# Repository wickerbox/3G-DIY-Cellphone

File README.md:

cellphone3g
===========

Hardware for a 3G cellphone based on GSM/GPRS Arduino shield and damellis' DIY Cellphone.

[David A Mellis' DIY Cellphone 2G 'Cellphone Module'](http://web.media.mit.edu/~mellis/gsm/)

That project uses the 2G Quectel M10 Module which is pin compatible with the 3G Quectel UC15 Module. 

[Quectel GSM/GPRS M10](http://www.quectel.com/product/prodetail.aspx?id=14)

[Quectel UMTS/HSDPA UC15](http://www.quectel.com/product/prodetail.aspx?id=64)

[Quectel M10 and UC15 Design Compatibility](http://top-electronics.com/news/26/quectel-uc15-and-m10-design-compatibility.html)

**Differences**

1. Slightly different 3.3V-4.3V (UC15) vs 3.3V-4.6V (M10). Using a 3.7V battery is fine. MCP73831 recharges the 3.7V battery from the USB ... if the unit is powered off USB, it's at 4.2V which is on the high end. which is a little too close for comfort so I'd want to replace it with a USIM is the same. 

1. Frequency bands are slightly different but not much.

1. Pinout from controller will have to change. 

**Vocabulary**

GSM - Global System for Mobile Communications, 2G  
GPRS - General Packet Radio Services, packet data service on 2G and 3G  
UMTS - Universal Mobile Telecommunications System, 3G  
HSDPA - High-Speed Downlink Packet Access, allows higher speeds 3G speeds

**Reference**

"GSM (Global System for Mobile Communications, originally Groupe Spécial Mobile), is a standard developed by the European Telecommunications Standards Institute (ETSI) to describe protocols for second generation (2G) digital cellular networks used by mobile phones." [Wikipedia](http://en.wikipedia.org/wiki/GSM)

"General packet radio service (GPRS) is a packet oriented mobile data service on the 2G and 3G cellular communication system's global system for mobile communications (GSM)." [Wikipedia](http://en.wikipedia.org/wiki/General_Packet_Radio_Service)

"UMTS specifies a complete network system, which includes the radio access network (UMTS Terrestrial Radio Access Network, or UTRAN), the core network (Mobile Application Part, or MAP) and the authentication of users via SIM (subscriber identity module) cards." [Wikipedia](http://en.wikipedia.org/wiki/Universal_Mobile_Telecommunications_System)

"High-Speed Downlink Packet Access (HSDPA) is an enhanced 3G (third-generation) mobile-telephony communications protocol in the High-Speed Packet Access (HSPA) family, also dubbed 3.5G, 3G+, or Turbo 3G, which allows networks based on Universal Mobile Telecommunications System (UMTS) to have higher data-transfer speeds and capacity." [Wikipedia](en.wikipedia.org/wiki/High-Speed_Downlink_Packet_Access)

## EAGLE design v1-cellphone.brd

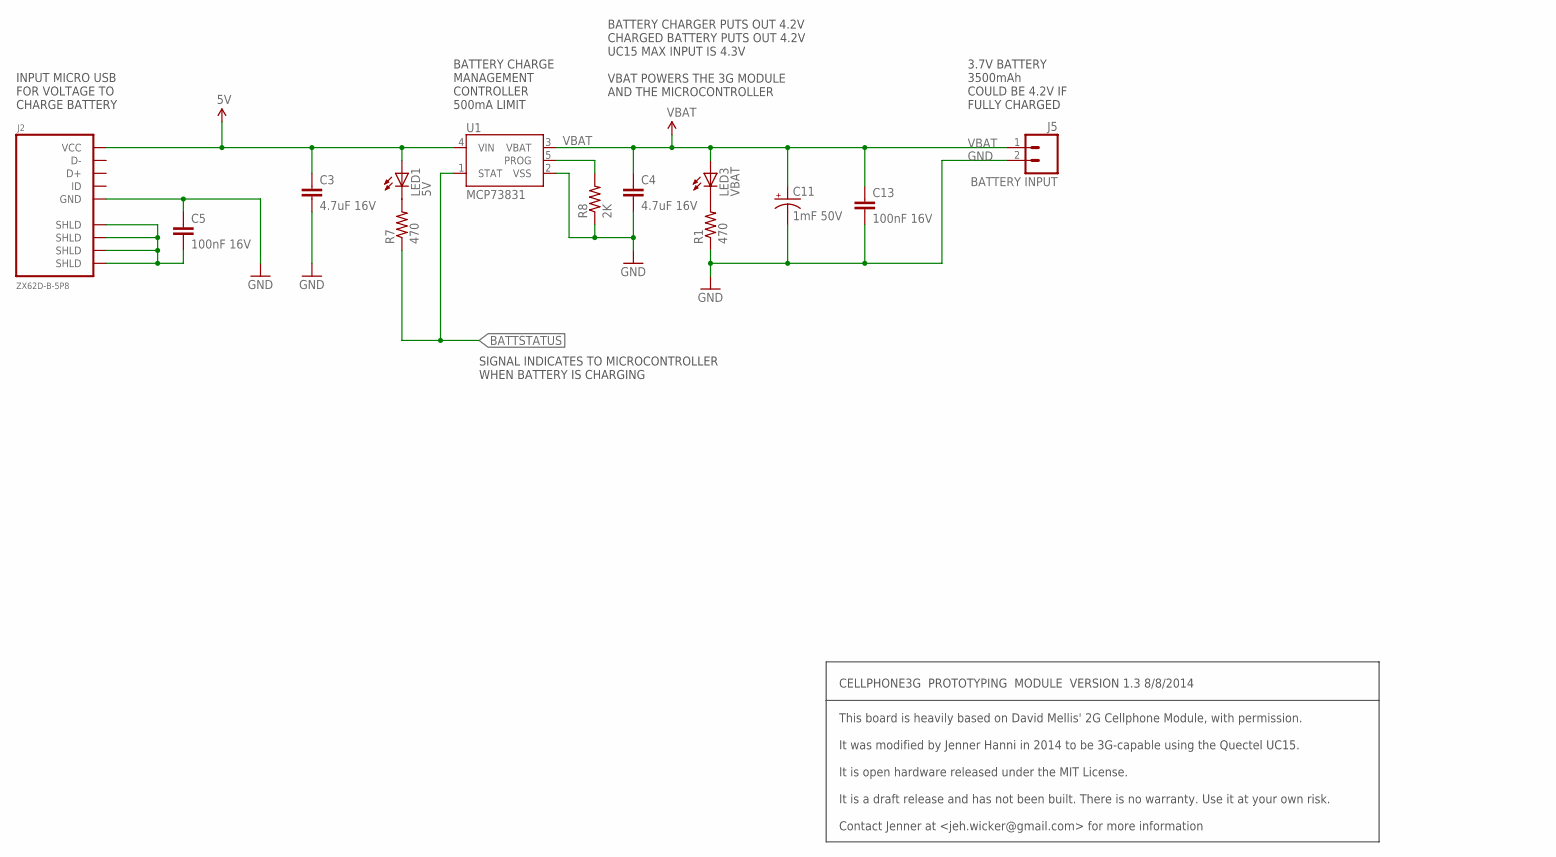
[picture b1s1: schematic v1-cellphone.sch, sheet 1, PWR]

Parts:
C3, C4: 4.7uF 16V; 0603-B
C5, C13: 100nF 16V; 0603-B
C11: 1mF 50V; CPOL-RADIAL-1000UF-25V
J2: ZX62D-B-5P8
J5: BATTERY INPUT; JST-2-SMD
LED1: 5V; CHIP-LED0603
LED3: VBAT; CHIP-LED0603
R1, R7: 470; 0603-B
R8: 2K; 0603-B
U1: MCP73831; SPARKFUN_SOT23-5

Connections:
5V: C3.1, J2.P1 (VCC), LED1.A, U1.4 (VIN); also elsewhere on the board
BATTSTATUS: R7.1, U1.1 (STAT); also elsewhere on the board
GND: C3.2, C4.2, C5.1, C11.2 (-), C13.2, J2.P5 (GND), J5.2 (1), R1.1, R8.1, U1.2 (VSS); also elsewhere on the board
unnamed: LED3.C, R1.2
unnamed: LED1.C, R7.2
PROG: R8.2, U1.5 (PROG)
SHLD: C5.2, J2.P$1 (SHLD), J2.P$2 (SHLD), J2.P$3 (SHLD), J2.P$4 (SHLD)
VBAT: C4.1, C11.1 (+), C13.1, J5.1 (2), LED3.A, U1.3 (VBAT); also elsewhere on the board

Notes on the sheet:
INPUT MICRO USB FOR VOLTAGE TO CHARGE BATTERY
BATTERY CHARGE MANAGEMENT CONTROLLER 500mA LIMIT
3.7V BATTERY 3500mAh COULD BE 4.2V IF FULLY CHARGED
BATTERY CHARGER PUTS OUT 4.2V CHARGED BATTERY PUTS OUT 4.2V UC15 MAX INPUT IS 4.3V VBAT POWERS THE 3G MODULE AND THE MICROCONTROLLER
CELLPHONE3G PROTOTYPING MODULE VERSION 1.3 8/8/2014
This board is heavily based on David Mellis' 2G Cellphone Module, with permission. It was modified by Jenner Hanni in 2014 to be 3G-capable using the Quectel UC15. It is open hardware released under the MIT License. It is a draft release and has not been built. There is no warranty. Use it at your 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
SIGNAL INDICATES TO MICROCONTROLLER WHEN BATTERY IS CHARGING

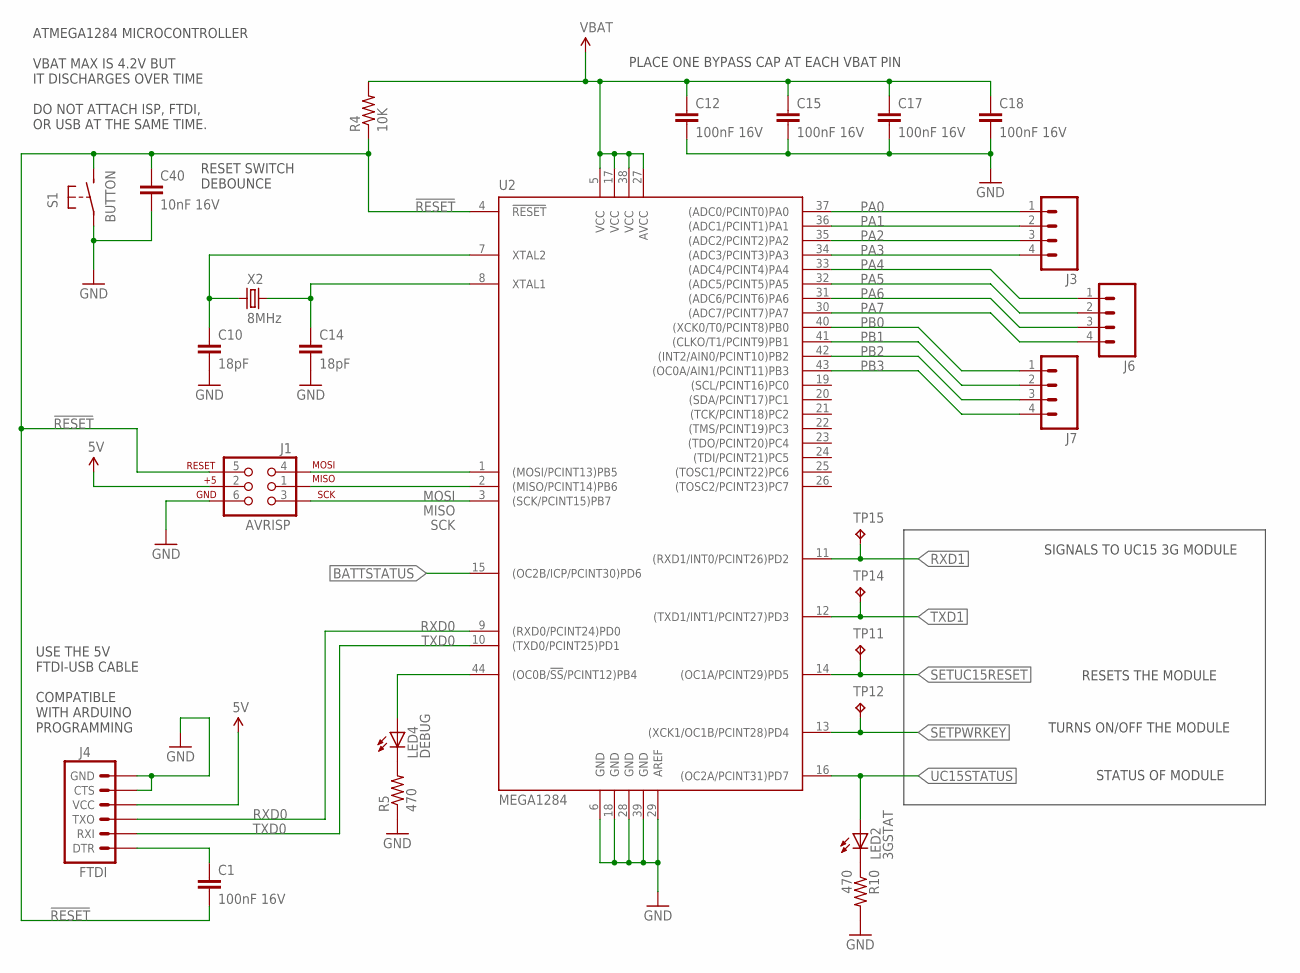
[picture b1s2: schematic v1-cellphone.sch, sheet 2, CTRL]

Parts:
C1, C12, C15, C17, C18: 100nF 16V; 0603-B
C10, C14: 18pF; 0603-B
C40: 10nF 16V; 0603-B
J1: AVRISP; SPARKFUN-CONNECTORS_2X3-NS
J3, J6, J7: M04LOCK; 1X04_LOCK
J4: FTDI; 1X06_LOCK
LED2: 3GSTAT; CHIP-LED0603
LED4: DEBUG; CHIP-LED0603
R4: 10K; 0603-B
R5, R10: 470; 0603-B
S1: BUTTON; CELLPHONE_B3U-1000P
TP11, TP12, TP14, TP15: TPPAD1-13; P1-13
U2: MEGA1284; AVR-5_TQFP44
X2: 8MHz; 2-SMD-5X3MM

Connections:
5V: J1.2 (2-5VCC), J4.4 (VCC); also elsewhere on the board
!RESET: C1.2, C40.1, J1.5 (5-RESET), R4.1, S1.P$2 (S), U2.4 (!RESET)
BATTSTATUS: U2.15 ((OC2B/ICP/PCINT30)PD6); also elsewhere on the board
DEBUGLED: LED4.A, U2.44 ((OC0B/!SS!/PCINT12)PB4)
GND: C10.2, C12.2, C14.2, C15.2, C17.2, C18.2, C40.2, J1.6 (6-GND), J4.5 (CTS), J4.6 (GND), R5.1, R10.2, S1.P$1, U2.6 (GND), U2.18 (GND), U2.28 (GND), U2.29 (AREF), U2.39 (GND); also elsewhere on the board
MISO: J1.1 (1-MISO), U2.2 ((MISO/PCINT14)PB6)
MOSI: J1.4 (4-MOSI), U2.1 ((MOSI/PCINT13)PB5)
unnamed: LED4.C, R5.2
unnamed: C1.1, J4.1 (DTR)
unnamed: LED2.C, R10.1
PA0: J3.1, U2.37 ((ADC0/PCINT0)PA0)
PA1: J3.2, U2.36 ((ADC1/PCINT1)PA1)
PA2: J3.3, U2.35 ((ADC2/PCINT2)PA2)
PA3: J3.4, U2.34 ((ADC3/PCINT3)PA3)
PA4: J6.1, U2.33 ((ADC4/PCINT4)PA4)
PA5: J6.2, U2.32 ((ADC5/PCINT5)PA5)
PA6: J6.3, U2.31 ((ADC6/PCINT6)PA6)
PA7: J6.4, U2.30 ((ADC7/PCINT7)PA7)
PB0: J7.1, U2.40 ((XCK0/T0/PCINT8)PB0)
PB1: J7.2, U2.41 ((CLKO/T1/PCINT9)PB1)
PB2: J7.3, U2.42 ((INT2/AIN0/PCINT10)PB2)
PB3: J7.4, U2.43 ((OC0A/AIN1/PCINT11)PB3)
RXD0: J4.3 (TXO), U2.9 ((RXD0/PCINT24)PD0)
RXD1: TP15.TP, U2.11 ((RXD1/INT0/PCINT26)PD2); also elsewhere on the board
SCK: J1.3 (3-SCK), U2.3 ((SCK/PCINT15)PB7)
SETPWRKEY: TP12.TP, U2.13 ((XCK1/OC1B/PCINT28)PD4); also elsewhere on the board
SETUC15RESET: TP11.TP, U2.14 ((OC1A/PCINT29)PD5); also elsewhere on the board
TXD0: J4.2 (RXI), U2.10 ((TXD0/PCINT25)PD1)
TXD1: TP14.TP, U2.12 ((TXD1/INT1/PCINT27)PD3); also elsewhere on the board
UC15STATUS: LED2.A, U2.16 ((OC2A/PCINT31)PD7); also elsewhere on the board
VBAT: C12.1, C15.1, C17.1, C18.1, R4.2, U2.5 (VCC), U2.17 (VCC), U2.27 (AVCC), U2.38 (VCC); also elsewhere on the board
XTAL1: C14.1, U2.8 (XTAL1), X2.P$2 (2)
XTAL2: C10.1, U2.7 (XTAL2), X2.P$1 (1)

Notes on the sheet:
PLACE ONE BYPASS CAP AT EACH VBAT PIN
USE THE 5V FTDI-USB CABLE COMPATIBLE WITH ARDUINO PROGRAMMING
TURNS ON/OFF THE MODULE
RESETS THE MODULE
STATUS OF MODULE
SIGNALS TO UC15 3G MODULE
ATMEGA1284 MICROCONTROLLER VBAT MAX IS 4.2V BUT IT DISCHARGES OVER TIME DO NOT ATTACH ISP, FTDI, OR USB AT THE SAME TIME.
RESET SWITCH DEBOUNCE

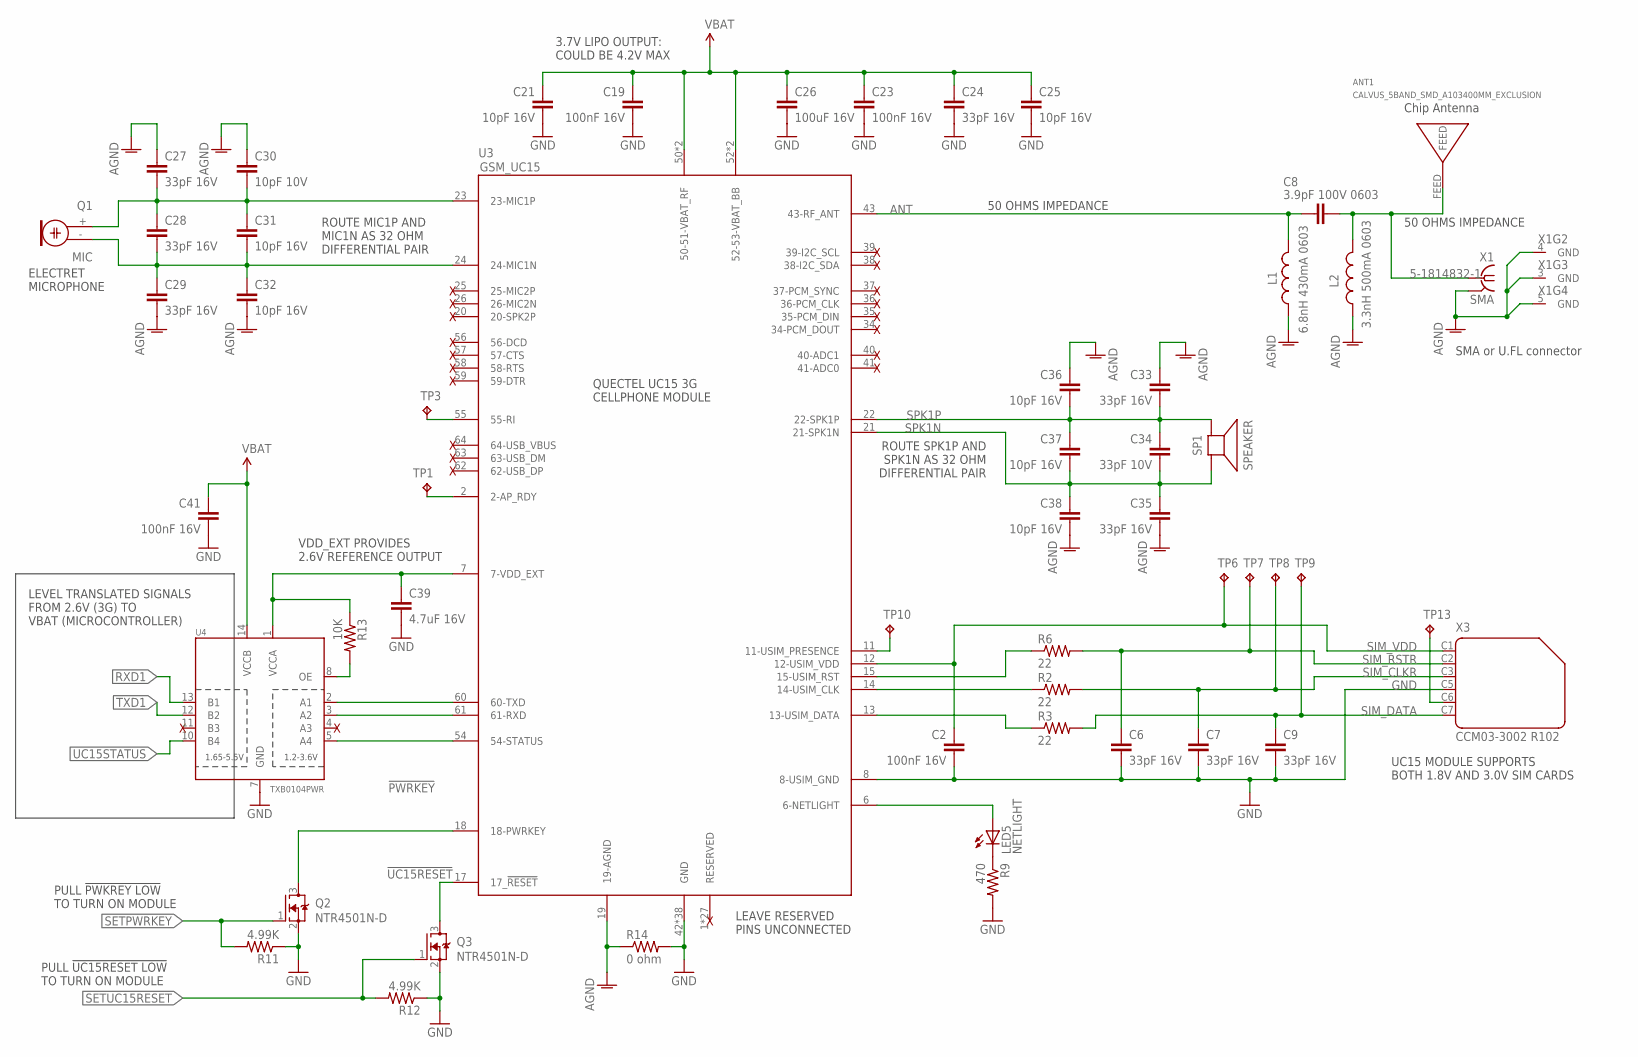
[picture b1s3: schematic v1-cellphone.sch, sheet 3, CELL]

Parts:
ANT1: CALVUS_5BAND_SMD_A103400MM_EXCLUSION; CALVUS_5BAND_SMD_A10340_0MM_EXCLUSION
C2, C19, C23, C41: 100nF 16V; 0603-B
C6, C7, C9, C24, C27, C28, C29, C33, C35: 33pF 16V; 0603-B
C8: 3.9pF 100V 0603; 0603-B
C21, C25, C31, C32, C36, C37, C38: 10pF 16V; 0603-B
C26: 100uF 16V; C1210K
C30: 10pF 10V; 0603-B
C34: 33pF 10V; 0603-B
C39: 4.7uF 16V; 0603-B
L1: 6.8nH 430mA 0603; 0603-B
L2: 3.3nH 500mA 0603; 0603-B
LED5: NETLIGHT; CHIP-LED0603
Q1: MIC; 9.7ELECTRET
Q2, Q3: NTR4501N-D; SOT-23
R2, R3, R6: 22; 0603-B
R9: 470; 0603-B
R11, R12: 4.99K; 0603-B
R13: 10K; 0603-B
R14: 0 ohm; 0603-B
SP1: SPEAKER; CELLPHONE_SPEAKER-6.4MM
TP1, TP3, TP6, TP7, TP8, TP9, TP10, TP13: TPPAD1-13; P1-13
U3: GSM_UC15; GSM_UC15_WITHOUT_EXCLUSION
U4: TXB0104PWR; TSSOP14
X1: SMA; CON-COAX_BU-SMA-V
X3: CCM03-3002 R102; SMARTPRJ_CON-AMPHENOL_C707_10M006_512_2

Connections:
!PWRKEY: Q2.3 (D), U3.18 (18-PWRKEY)
!UC15RESET: Q3.3 (D), U3.17 (17_!RESET)
AGND: C27.1, C29.2, C30.1, C32.2, C33.1, C35.2, C36.1, C38.2, L1.1, L2.1, R14.1, U3.19 (19-AGND), X1.2 (GND), X1.3 (GND), X1.4 (GND), X1.5 (GND)
ANT: C8.1, L1.2, U3.43 (43-RF_ANT)
ANTENNA: ANT1.FEED, C8.2, L2.2, X1.1
GND: C2.2, C6.2, C7.2, C9.2, C19.2, C21.2, C23.2, C24.2, C25.2, C26.2, C39.2, C41.2, Q2.2 (S), Q3.2 (S), R9.2, R11.1, R12.1, R14.2, U3.8 (8-USIM_GND), U3.42 (GND), U3.44 (GND), U3.45 (GND), U3.46 (GND), U3.47 (GND), U3.48 (GND), U3.49 (GND), U3.65 (GND), U3.67 (GND), U3.68 (GND), U3.81 (GND), U3.82 (GND), U3.83 (GND), U3.84 (GND), U3.85 (GND), U3.86 (GND), U3.87 (GND), U3.88 (GND), U3.89 (GND), U3.90 (GND), U3.91 (GND), U3.92 (GND), U3.93 (GND), U3.94 (GND), U3.95 (GND), U3.96 (GND), U3.97 (GND), U3.98 (GND), U3.99 (GND), U3.100 (GND), U3.101 (GND), U3.102 (GND), U3.103 (GND), U3.104 (GND), U3.105 (GND), U3.106 (GND), U3.107 (GND), U3.108 (GND), U4.7 (GND), X3.C5 (4); also elsewhere on the board
MIC1N: C28.2, C29.1, C31.2, C32.1, Q1.- (1), U3.24 (24-MIC1N)
MIC1P: C27.2, C28.1, C30.2, C31.1, Q1.+ (2), U3.23 (23-MIC1P)
unnamed: R3.1, U3.13 (13-USIM_DATA)
unnamed: LED5.C, R9.1
unnamed: TP13.TP, X3.C6 (5)
unnamed: TP1.TP, U3.2 (2-AP_RDY)
unnamed: TP3.TP, U3.55 (55-RI)
unnamed: U3.60 (60-TXD), U4.2 (A1)
unnamed: U3.61 (61-RXD), U4.3 (A2)
unnamed: U3.54 (54-STATUS), U4.5 (A4)
NETLIGHT: LED5.A, U3.6 (6-NETLIGHT)
OE: R13.2, U4.8 (OE)
PRESENCE: TP10.TP, U3.11 (11-USIM_PRESENCE)
RXD1: U4.13 (B1); also elsewhere on the board
SETPWRKEY: Q2.1 (G), R11.2; also elsewhere on the board
SETUC15RESET: Q3.1 (G), R12.2; also elsewhere on the board
SIM_CLK: R2.1, U3.14 (14-USIM_CLK)
SIM_CLKR: C7.1, R2.2, TP8.TP, X3.C3 (3)
SIM_DATA: C9.1, R3.2, TP9.TP, X3.C7 (6)
SIM_RST: R6.1, U3.15 (15-USIM_RST)
SIM_RSTR: C6.1, R6.2, TP7.TP, X3.C2 (2)
SIM_VDD: C2.1, TP6.TP, U3.12 (12-USIM_VDD), X3.C1 (1)
SPK1N: C34.2, C35.1, C37.2, C38.1, SP1.NEG, U3.21 (21-SPK1N)
SPK1P: C33.2, C34.1, C36.2, C37.1, SP1.POS, U3.22 (22-SPK1P)
TXD1: U4.12 (B2); also elsewhere on the board
UC15STATUS: U4.10 (B4); also elsewhere on the board
VBAT: C19.1, C21.1, C23.1, C24.1, C25.1, C26.1, C41.1, U3.50 (50-51-VBAT_RF), U3.51 (50-51-VBAT_RF), U3.52 (52-53-VBAT_BB), U3.53 (52-53-VBAT_BB), U4.14 (VCCB); also elsewhere on the board
VDD_EXT: C39.1, R13.1, U3.7 (7-VDD_EXT), U4.1 (VCCA)

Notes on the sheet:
Chip Antenna
SMA or U.FL connector
UC15 MODULE SUPPORTS BOTH 1.8V AND 3.0V SIM CARDS
LEAVE RESERVED PINS UNCONNECTED
QUECTEL UC15 3G CELLPHONE MODULE
ELECTRET MICROPHONE
ROUTE MIC1P AND MIC1N AS 32 OHM DIFFERENTIAL PAIR
ROUTE SPK1P AND SPK1N AS 32 OHM DIFFERENTIAL PAIR
50 OHMS IMPEDANCE
3.7V LIPO OUTPUT: COULD BE 4.2V MAX
LEVEL TRANSLATED SIGNALS FROM 2.6V (3G) TO VBAT (MICROCONTROLLER)
PULL !PWKREY LOW TO TURN ON MODULE
PULL !UC15RESET LOW TO TURN ON MODULE
VDD_EXT PROVIDES 2.6V REFERENCE OUTPUT

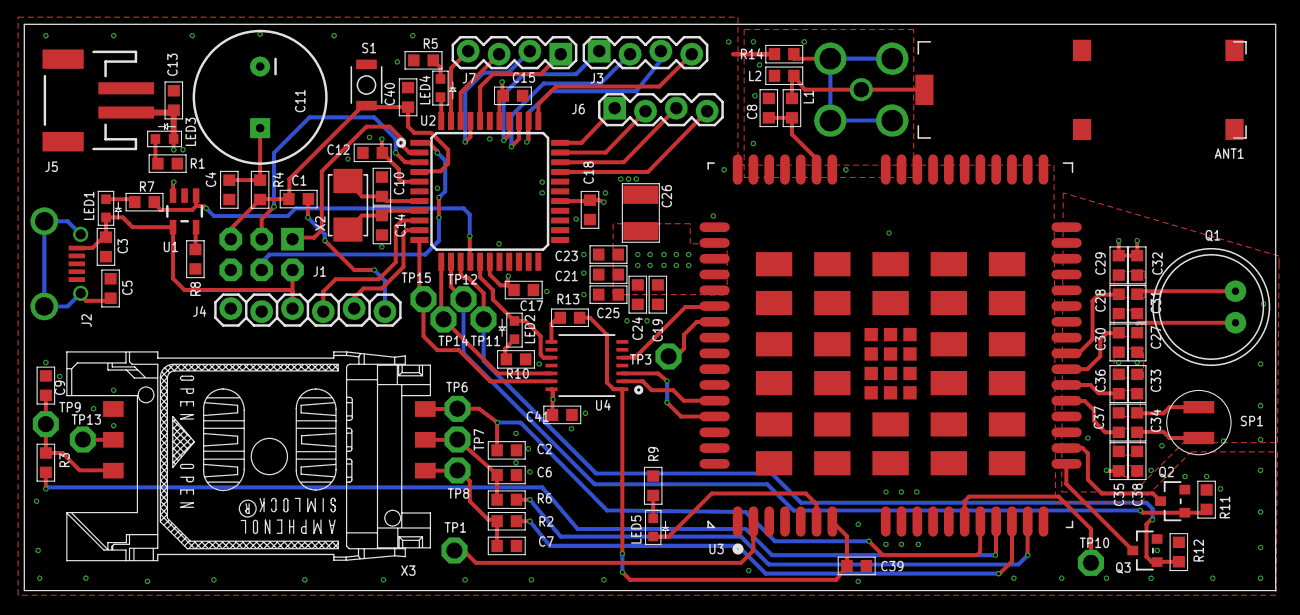
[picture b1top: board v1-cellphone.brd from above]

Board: 4 copper layers, 103.1 x 46.7 mm, 91 parts (1 on the bottom side), 64 nets.

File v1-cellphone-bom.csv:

Item	Qty	Refdes	Description	Mfr	Mfr P/N	Digikey P/N	Unit Cost	Total Cost	Notes
1	1	ANT1	Antenna, Chip, Calvus, 824-960MHZ SMD	Antenova	A10340	627-1022-1-ND	$4.78	$4.78	
2	11	C1, C2, C5, C12, C13, C15, C17, C18, C19, C23, C41	Capacitor, Ceramic, 100nF 16V 5% X7R 0603	Samsung	CL10B104JO8NNNC	1276-1061-1-ND	$0.11	$1.21	
3	3	C3, C4, C39	Capacitor, Ceramic, 4.7uF 16V 10% X7R 0603	Samsung	CL10A475KO8NNNC	1276-1784-1-ND	$0.26	$0.78	
4	1	C8	Capacitor, Ceramic, 3.9pF 100V NP0 0603	Murata	GQM1885C2A3R9BB01D	490-4841-1-ND	$0.72	$0.72	
5	10	C6, C7, C9, C24, C27, C28, C29, C33, C34, C35	Capacitor, Ceramic, 33pF 16V 5% X7R 0603	AVX	0603YC330JAT2A	478-6211-1-ND	$0.12	$1.20	
6	1	C11	Capacitor, Aluminum, 1000uF 50V 20% Radial	Nichicon	UVR1H102MHD	493-1111-ND	$0.96	$0.96	
7	2	C10, C14	Capacitor, Ceramic, 18pF 16V 5% NP0 0603	Kemet	C0603C180J4GACTU	399-11141-1-ND	$0.25	$0.50	
8	1	C40	Capacitor, Ceramic, 10nF 16V 10% X7R 0603	Samsung	CL10B103KO8NNNC	1276-1926-1-ND	$0.10	$0.10	
9	1	C26	Capacitor, Ceramic, 100uF 16V 20% X5R 1210	Kemet	EMK325ABJ107MM-T	587-3152-1-ND	$2.30	$2.30	
10	8	C21, C25, C30, C31, C32, C36, C37, C38	Capacitor, Ceramic, 10pF 50V 5% NP0 0603	Samsung	CL10C100JB8NCNC	1276-2154-1-ND	$0.10	$0.80	
11	1	J1	Connector, AVR ISP, 2x3, Male, R/A, 0.1”	Harwin	M20-8760342	952-1922-ND	$0.43	$0.43	
12	1	J2	Connector, Micro USB-B, SMD with TH Shell	Hirose	ZX62D-B-5P8	H11610CT-ND	$1.20	$1.20	
13	3	J3,J6,J7	Connector, Straight, Female, Unshrouded, 4-pin, 0.1”	Sullins	PPPC041LFBN-RC	S7037-ND	$0.60	$1.80	
14	1	J4	Connector, Straight, Male, Unshrouded, 6-pin, 0.1”	Harwin	M20-9990645	952-2269-ND	$0.26	$0.26	
15	1	J5	Connector, PH Series, Battery, 2-pin, 2MM, SMT	JST	S2B-PH-SM4-TB(LF)(SN)	455-1749-1-ND	$0.56	$0.56	
16	1	L1	Inductor, 6.8nH 430mA 0603	Murata	LQG18HN6N8J00D	490-1108-1-ND	$0.21	$0.21	
17	1	L2	Inductor, 3.3nH 500mA 0603	Murata	LQG18HN3N3S00D	490-1104-1-ND	$0.21	$0.21	
18	5	LED1, LED2, LED3, LED4, LED5	LED, Chip, Pure Green, SMD, 0603	Stanley	BG1111C-TR	404-1005-1-ND	$0.57	$2.85	
19	1	Q1	Mic, Electret, Conditioned Analog Omni -44dB	CUI	CMA-4544PF-W	102-1721-ND	$0.96	$0.96	
20	2	Q2, Q3	MOSFET, N-CH, 20V 3.2A SOT-23	ON Semi	NTR4501NT1G	NTR4501NT1GOSCT-ND	$0.59	$1.18	
21	3	R2, R3, R6	Resistor, 22 OHM 1/4W 5% 0603 	Rohm	ESR03EZPJ220	RHM22DCT-ND	$0.10	$0.30	
22	5	R1, R5, R7, R9, R10	Resistor, 470 OHM 1/4W 5% 0603 	Rohm	ESR03EZPJ471	RHM470DCT-ND	$0.10	$0.50	
23	2	R11, R12	Resistor, 4.99K 1/8W 1% 0603	Stackpole	RNCP0603FTD4K99	RNCP0603FTD4K99CT-ND	$0.05	$0.10	
24	1	R8	Resistor, 2K 1/8W 1% 0603	Stackpole	RNCP0603FTD2K00	RNCP0603FTD2K00CT-ND	$0.05	$0.05	
25	1	R14	Resistor, 0 OHM 1/8W JUMP 0603	Vishay	MCT06030Z0000ZP500	MCT0603-0.0-ZZCT-ND	$0.13	$0.13	
26	2	R4, R13	Resistor, 10K 1/8W 1% 0603	Stackpole	RNCP0603FTD10K0	RNCP0603FTD10K0CT-ND	$0.05	$0.10	
27	1	S1	Button, Tactile Switch, SPST-NO 0.05A 12V	Omron	B3U-1000P	SW1020CT-ND	$1.25	$1.25	
28	1	SP1	Speaker, Receiver, 100Hz-9.5kHz 55.5ohm	Knowles	SR6438NWS-000	423-1142-ND	$6.27	$6.27	
29	1	U1	IC, Battery Charge Controller, LiPo, 4.2V, 20T23-5	Microchip	MCP73831T-2ACI/OT	MCP73831T-2ACI/OTCT-ND	$0.67	$0.67	
30	1	U2	IC, Microcontroller, 8-bit 128KB FLASH 44TQFP	Atmel	ATMEGA1284P-AUR	ATMEGA1284P-AURCT-ND	$8.99	$8.99	
31	1	U3	GSM Module, UC15 3G	Quectel	UC15	SEE NOTE	$65.00	$65.00	Order through D'Art Perfect (http://www.d-art-perfect.com/#!product/prd1/1837100545/uc15)
32	1	U4	IC, Volt Level Translator, 14TSSOP	TI	TXB0104PWR	296-21929-1-ND	$1.69	$1.69	
33	1	X1	Connector, SMA Jack, R/A, 50ohm TH	Emerson	142-0701-301	J501-ND	$7.76	$7.76	
34	1	X2	Crystal, 8MHz, 18pF SMD	Abracon	ABM3-8.000MHZ-D2Y-T	535-10630-1-ND	$1.09	$1.09	
35	1	X3	Connector, Smart Card (SIM), Hinged, 6-pin SMD	C&K	C707 10M006 5002	361-1020-1-ND	$1.03	$1.03	
							SUM	$117.94	Total cost with cell module
							SUM-CELL	$52.94	Total cost without cell module

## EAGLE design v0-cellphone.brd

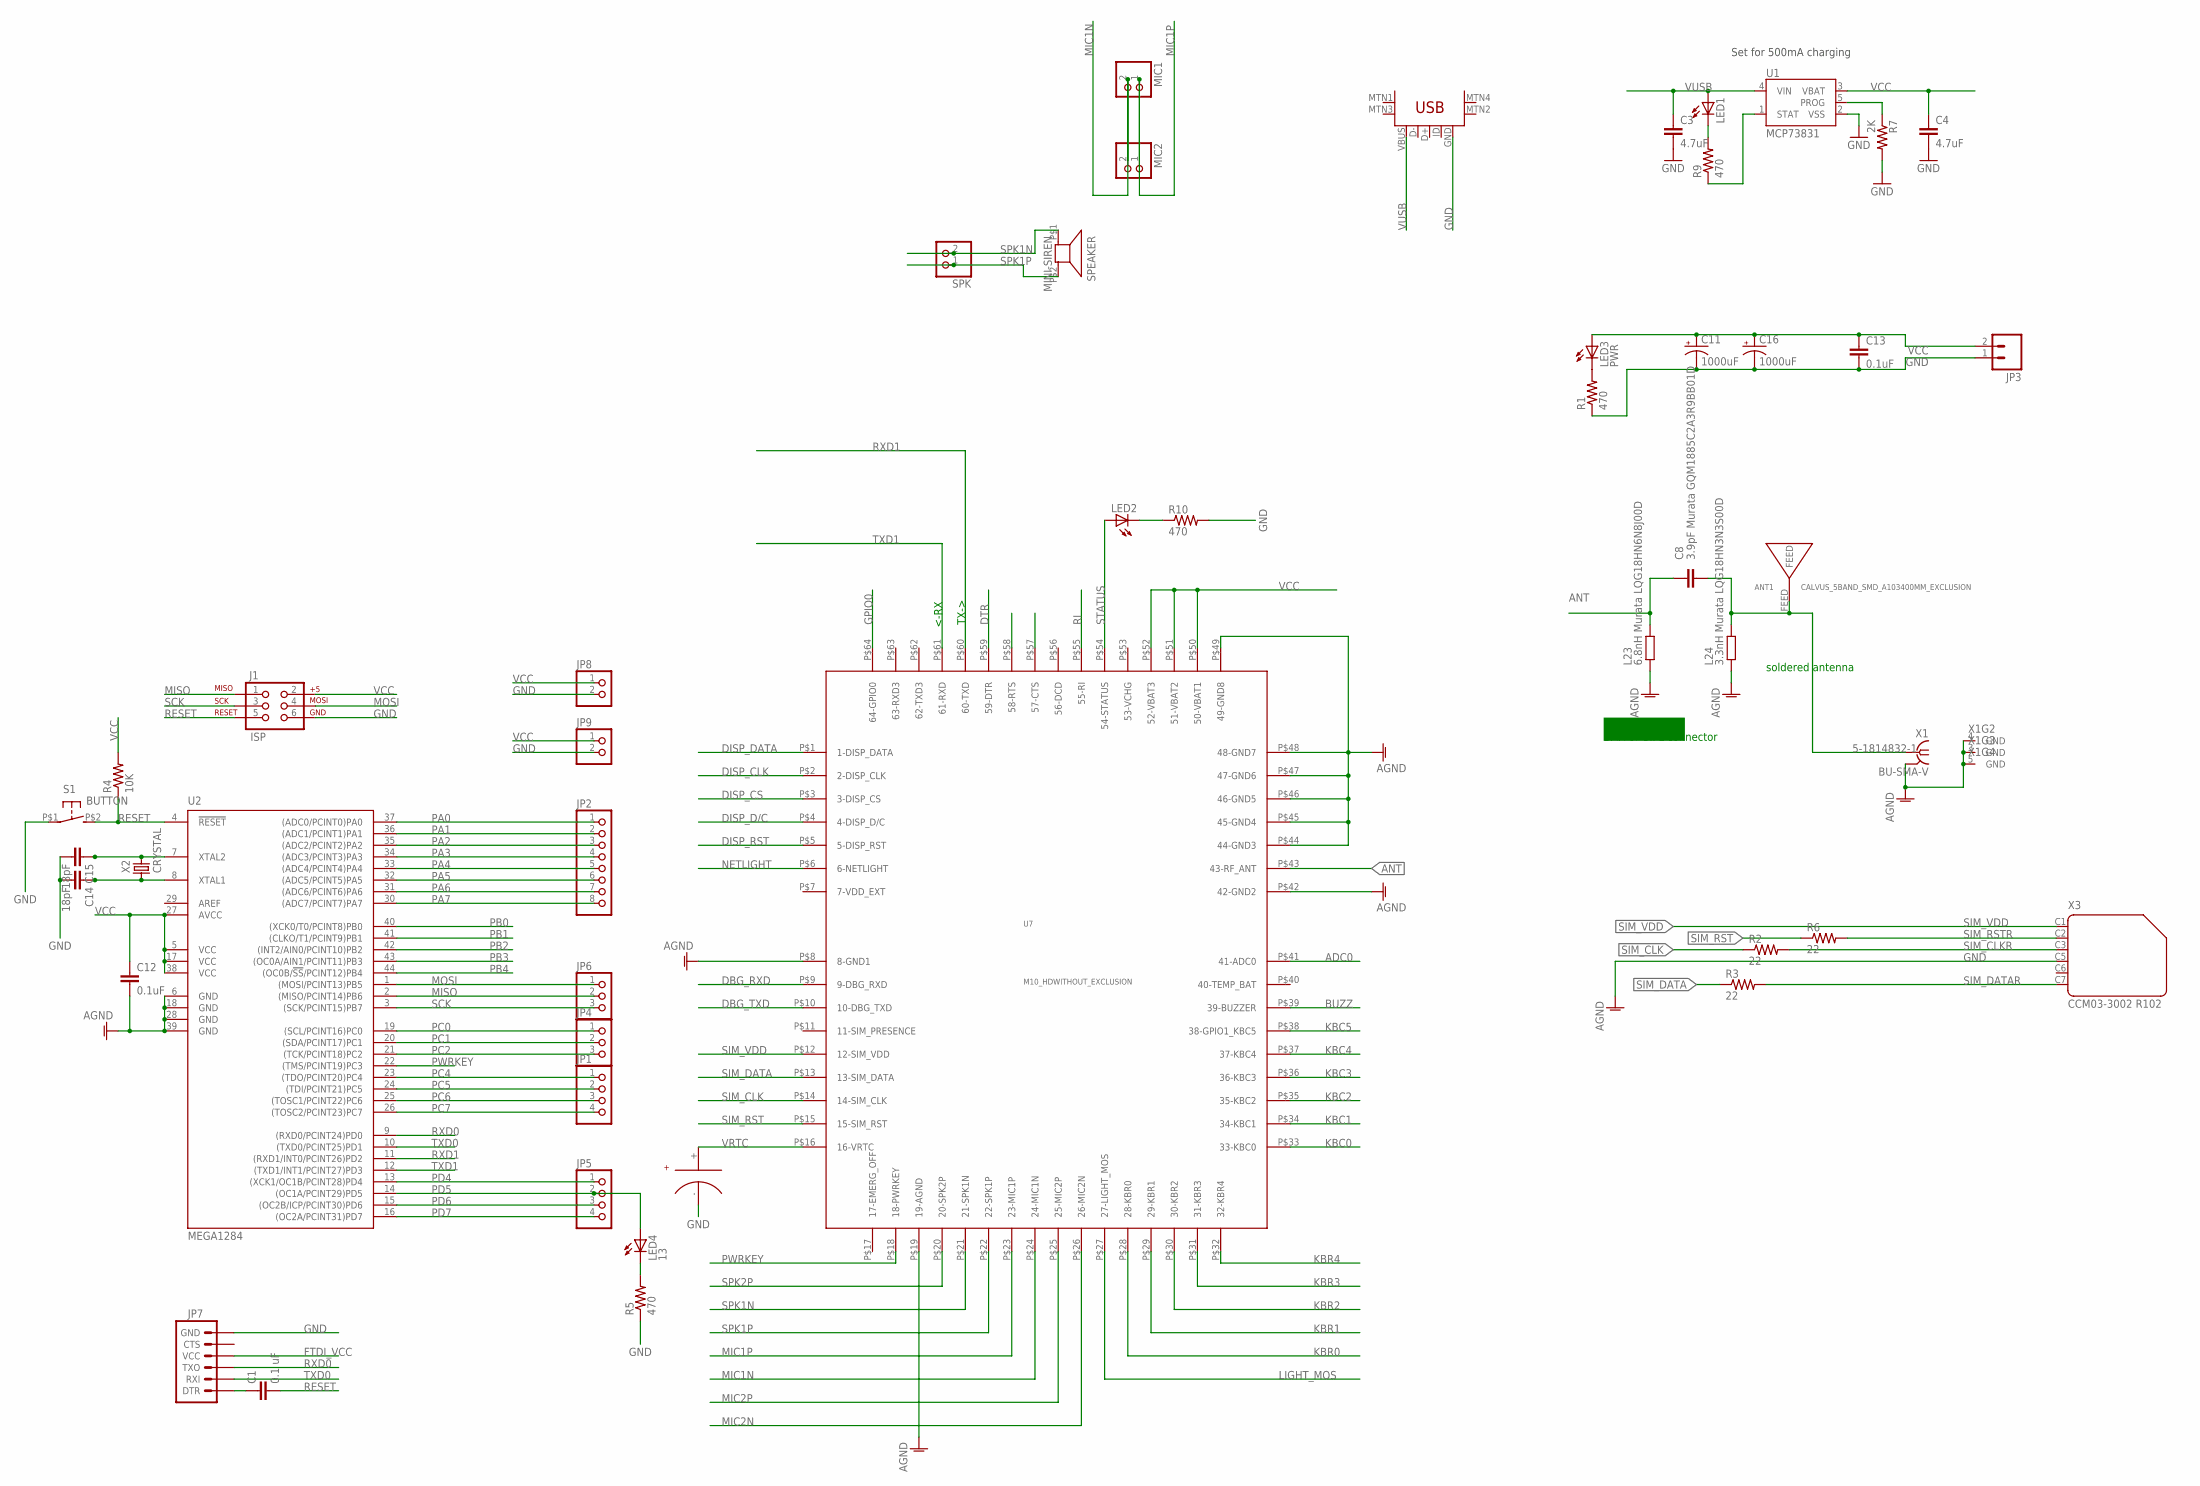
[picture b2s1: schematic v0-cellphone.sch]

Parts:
ANT1: CALVUS_5BAND_SMD_A103400MM_EXCLUSION; CALVUS_5BAND_SMD_A10340_0MM_EXCLUSION
C1: 0.1 uF; C1206
C2: SUPERCAPPAS; 414-VA5R
C3, C4: 4.7uF; C1206
C8: 3.9pF Murata GQM1885C2A3R9BB01D; C0603-ROUND
C11, C16: 1000uF; D/7343-31R
C12, C13: 0.1uF; C1206
C14, C15: 18pF; C1206
J1: ISP; 2X3-NS
J2: USB-MINIB-5PIN; USB-MINIB
JP1, JP5: PINHD-1X4; 1X04
JP2: PINHD-1X8; 1X08
JP3: M02-JST-2MM-SMT; JST-2-SMD
JP4, JP6: PINHD-1X3; 1X03
JP7: ARDUINO_SERIAL_PROGRAMSMD-NOHOLES; 1X06-SMD-NOHOLES
JP8, JP9: PINHD-1X2; 1X02
L23: 6.8nH Murata LQG18HN6N8J00D; R0603-ROUND
L24: 3.3nH Murata LQG18HN3N3S00D; R0603-ROUND
LED1, LED2: LEDSMT1206; 1206
LED3: PWR; 1206
LED4: 13; 1206
MIC1, MIC2: PINHD-1X2; 1X02
R1, R5, R9, R10: 470; R1206
R2, R3, R6: 22; R1206
R4: 10K; R1206
R7: 2K; R1206
S1: BUTTON; B3U-1000P
SPEAKER: MINI-SIREN; SPEAKER-6.4MM
SPK: PINHD-1X2; 1X02
U1: MCP73831; SOT23-5
U2: MEGA1284; TQFP44
U7: M10_HDWITHOUT_EXCLUSION; M10_HD_WITHOUT_EXCLUSION
X1: BU-SMA-V
X2: CRYSTAL; 2-SMD-5X3MM
X3: CCM03-3002 R102; CON-AMPHENOL_C707_10M006_512_2

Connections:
ADC0: U7.P$41 (41-ADC0)
ANT: C8.1, L23.2, U7.P$43 (43-RF_ANT)
ANTENA: ANT1.FEED, C8.2, L24.2, X1.1
AREF: U2.29 (AREF)
BUZZ: U7.P$39 (39-BUZZER)
DBG_RXD: U7.P$9 (9-DBG_RXD)
DBG_TXD: U7.P$10 (10-DBG_TXD)
DISP_CLK: U7.P$2 (2-DISP_CLK)
DISP_CS: U7.P$3 (3-DISP_CS)
DISP_D/C: U7.P$4 (4-DISP_D/C)
DISP_DATA: U7.P$1 (1-DISP_DATA)
DISP_RST: U7.P$5 (5-DISP_RST)
DTR: U7.P$59 (59-DTR)
FTDI_VCC: JP7.4 (VCC)
GND: C2.-, C3.2, C4.2, C11.-, C12.2, C13.2, C14.2, C15.2, C16.-, J1.6, J2.GND, JP3.1 (2), JP7.6 (GND), JP8.2, JP9.2, L23.1, L24.1, R1.1, R5.1, R7.2, R10.2, S1.P$1, U1.2 (VSS), U2.6 (GND), U2.18 (GND), U2.28 (GND), U2.39 (GND), U7.P$8 (8-GND1), U7.P$19 (19-AGND), U7.P$42 (42-GND2), U7.P$44 (44-GND3), U7.P$45 (45-GND4), U7.P$46 (46-GND5), U7.P$47 (47-GND6), U7.P$48 (48-GND7), U7.P$49 (49-GND8), X1.2 (GND), X1.3 (GND), X1.4 (GND), X1.5 (GND), X3.C5 (4)
GPIO0: U7.P$64 (64-GPIO0)
KBC0: U7.P$33 (33-KBC0)
KBC1: U7.P$34 (34-KBC1)
KBC2: U7.P$35 (35-KBC2)
KBC3: U7.P$36 (36-KBC3)
KBC4: U7.P$37 (37-KBC4)
KBC5: U7.P$38 (38-GPIO1_KBC5)
KBR0: U7.P$28 (28-KBR0)
KBR1: U7.P$29 (29-KBR1)
KBR2: U7.P$30 (30-KBR2)
KBR3: U7.P$31 (31-KBR3)
KBR4: U7.P$32 (32-KBR4)
LIGHT_MOS: U7.P$27 (27-LIGHT_MOS)
MIC1N: MIC1.2, MIC2.2, U7.P$24 (24-MIC1N)
MIC1P: MIC1.1, MIC2.1, U7.P$23 (23-MIC1P)
MIC2N: U7.P$26 (26-MIC2N)
MIC2P: U7.P$25 (25-MIC2P)
MISO: J1.1, JP6.2, U2.2 ((MISO/PCINT14)PB6)
MOSI: J1.4, JP6.1, U2.1 ((MOSI/PCINT13)PB5)
unnamed: LED3.C, R1.2
unnamed: LED4.C, R5.2
unnamed: C1.1, JP7.1 (DTR)
unnamed: C15.1, U2.7 (XTAL2), X2.P$2 (2)
unnamed: C14.1, U2.8 (XTAL1), X2.P$1 (1)
unnamed: R9.1, U1.1 (STAT)
unnamed: LED1.C, R9.2
unnamed: LED2.C, R10.1
NETLIGHT: U7.P$6 (6-NETLIGHT)
PA0: JP2.1, U2.37 ((ADC0/PCINT0)PA0)
PA1: JP2.2, U2.36 ((ADC1/PCINT1)PA1)
PA2: JP2.3, U2.35 ((ADC2/PCINT2)PA2)
PA3: JP2.4, U2.34 ((ADC3/PCINT3)PA3)
PA4: JP2.5, U2.33 ((ADC4/PCINT4)PA4)
PA5: JP2.6, U2.32 ((ADC5/PCINT5)PA5)
PA6: JP2.7, U2.31 ((ADC6/PCINT6)PA6)
PA7: JP2.8, U2.30 ((ADC7/PCINT7)PA7)
PB0: U2.40 ((XCK0/T0/PCINT8)PB0)
PB1: U2.41 ((CLKO/T1/PCINT9)PB1)
PB2: U2.42 ((INT2/AIN0/PCINT10)PB2)
PB3: U2.43 ((OC0A/AIN1/PCINT11)PB3)
PB4: U2.44 ((OC0B/!SS!/PCINT12)PB4)
PC0: JP4.1, U2.19 ((SCL/PCINT16)PC0)
PC1: JP4.2, U2.20 ((SDA/PCINT17)PC1)
PC2: JP4.3, U2.21 ((TCK/PCINT18)PC2)
PC4: JP1.1, U2.23 ((TDO/PCINT20)PC4)
PC5: JP1.2, U2.24 ((TDI/PCINT21)PC5)
PC6: JP1.3, U2.25 ((TOSC1/PCINT22)PC6)
PC7: JP1.4, U2.26 ((TOSC2/PCINT23)PC7)
PD4: JP5.1, U2.13 ((XCK1/OC1B/PCINT28)PD4)
PD5: JP5.2, LED4.A, U2.14 ((OC1A/PCINT29)PD5)
PD6: JP5.3, U2.15 ((OC2B/ICP/PCINT30)PD6)
PD7: JP5.4, U2.16 ((OC2A/PCINT31)PD7)
PROG: R7.1, U1.5 (PROG)
PWRKEY: U2.22 ((TMS/PCINT19)PC3), U7.P$18 (18-PWRKEY)
RESET: C1.2, J1.5, R4.1, S1.P$2 (S), U2.4 (!RESET)
RI: U7.P$55 (55-RI)
RXD0: JP7.3 (TXO), U2.9 ((RXD0/PCINT24)PD0)
RXD1: U2.11 ((RXD1/INT0/PCINT26)PD2), U7.P$60 (60-TXD)
SCK: J1.3, JP6.3, U2.3 ((SCK/PCINT15)PB7)
SIM_CLK: R2.1, U7.P$14 (14-SIM_CLK)
SIM_CLKR: R2.2, X3.C3 (3)
SIM_DATA: R3.1, U7.P$13 (13-SIM_DATA)
SIM_DATAR: R3.2, X3.C7 (6)
SIM_RST: R6.1, U7.P$15 (15-SIM_RST)
SIM_RSTR: R6.2, X3.C2 (2)
SIM_VDD: U7.P$12 (12-SIM_VDD), X3.C1 (1)
SPK1N: SPEAKER.P$1 (1), SPK.2, U7.P$21 (21-SPK1N)
SPK1P: SPEAKER.P$2 (2), SPK.1, U7.P$22 (22-SPK1P)
SPK2P: U7.P$20 (20-SPK2P)
STATUS: LED2.A, U7.P$54 (54-STATUS)
TXD0: JP7.2 (RXI), U2.10 ((TXD0/PCINT25)PD1)
TXD1: U2.12 ((TXD1/INT1/PCINT27)PD3), U7.P$61 (61-RXD)
VCC: C4.1, C11.+, C12.1, C13.1, C16.+, J1.2, JP3.2 (1), JP8.1, JP9.1, LED3.A, R4.2, U1.3 (VBAT), U2.5 (VCC), U2.17 (VCC), U2.27 (AVCC), U2.38 (VCC), U7.P$50 (50-VBAT1), U7.P$51 (51-VBAT2), U7.P$52 (52-VBAT3)
VRTC: C2.+, U7.P$16 (16-VRTC)
VUSB: C3.1, J2.VBUS, LED1.A, U1.4 (VIN)

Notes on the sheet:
soldered antenna
SMA or U.FL connector
TX->
<-RX
Set for 500mA charging

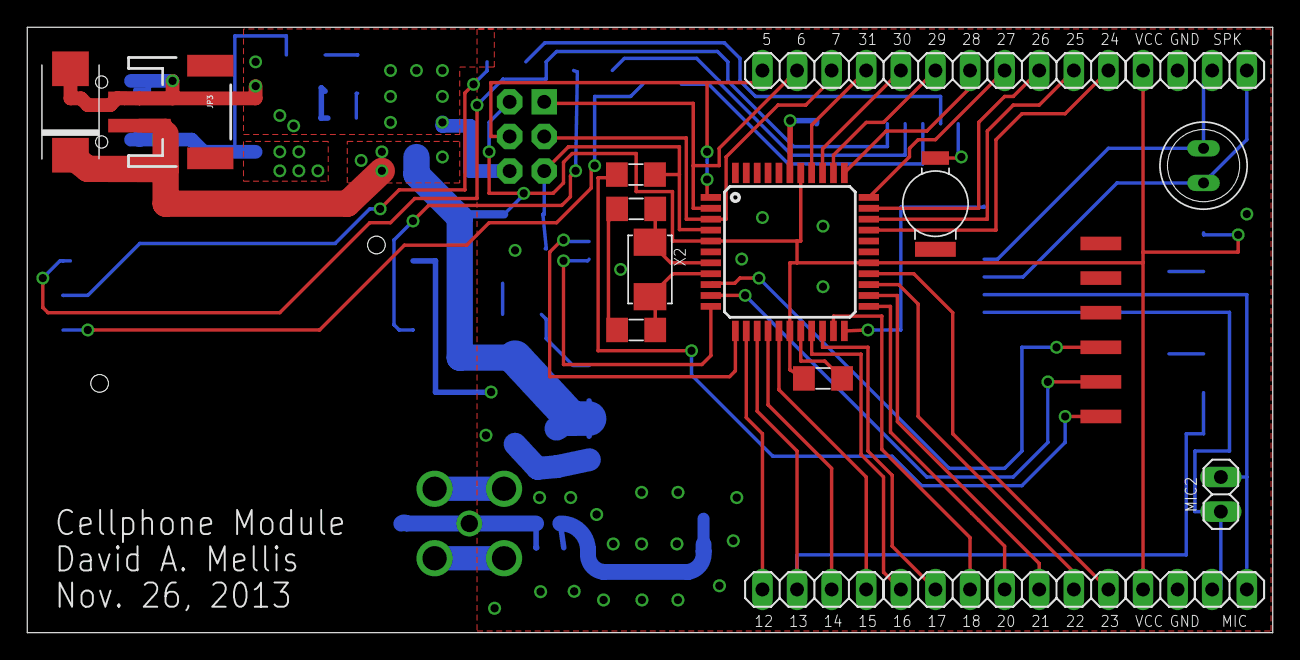
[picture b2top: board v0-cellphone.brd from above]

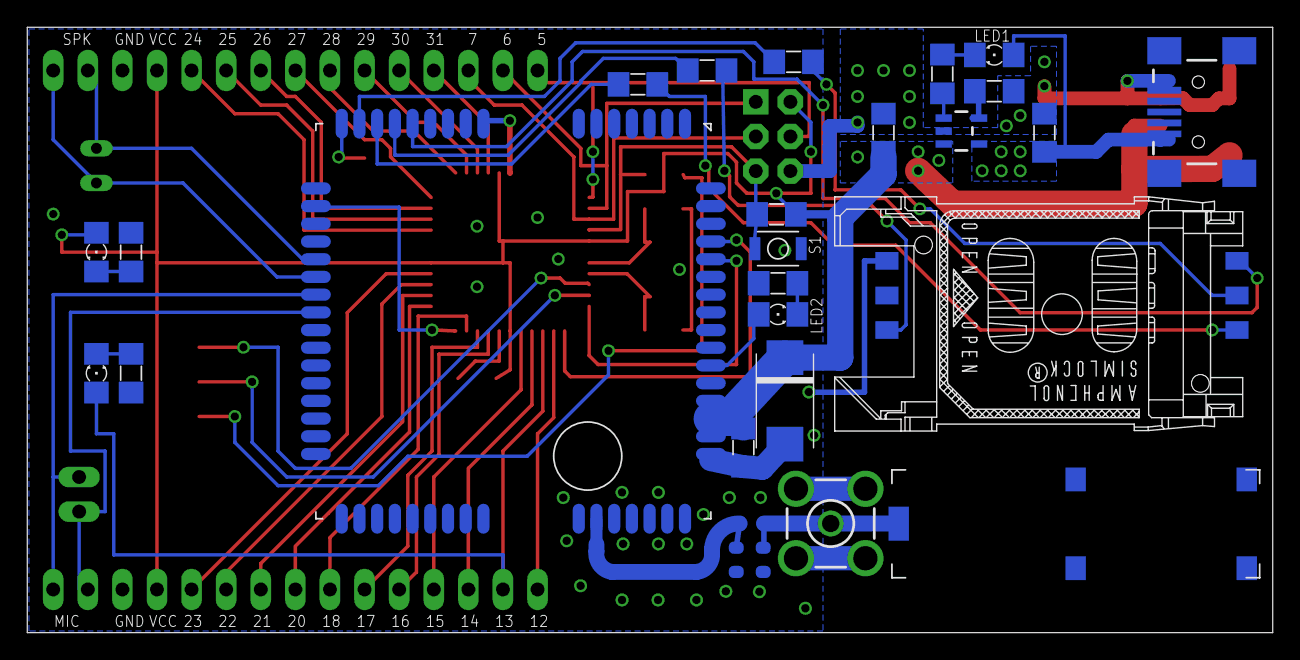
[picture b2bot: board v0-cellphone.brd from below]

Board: 2 copper layers, 91.4 x 44.5 mm, 49 parts (28 on the bottom side), 55 nets.

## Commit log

2014-07-19 Figured out how to replace M10 with UC15.
2014-07-26 Added reference eagle schematic from damellis' cellphone2hw
2014-07-26 Added reference library.
2014-07-26 Did a first pass through all parts of circuit. Annotated schematic. Made changes to library.
2014-08-02 Ready for review at diy devices.
2014-08-02 Added notes.
2014-08-03 Version 1.2 with diode and power changes, package fixes to 0603.
2014-08-08 Major power changes. Fixed 2.6V signal lines. Ready for review.
2014-08-08 Added caps, made frames same size.
2014-08-09 Made proper BOM of new board.
2014-08-09 Verified packages. Minor tweaks throughout.
2014-08-09 All tracks routed. Needs review and impedance checks.
2014-08-10 Fixed UC15 package. Passes ERC, DRC. Cleaned silk.
2014-08-11 Final for release. Passes ERC, DRC.
2014-08-11 Fixed format problem.
2014-08-12 Trying to fix TSV error
2014-08-12 Nope, that didn't work.
2014-08-12 Better formatting on the TSV file?
2014-08-12 Fixed.
2014-08-12 CSV fails because it ought to be TSV.
2014-08-30 Fixed switched R2 and C7 silkscreen labels.

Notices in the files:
parts and their libraries:
SparkFun-Connectors: Licensing: CC v3.0 Share-Alike You are welcome to use this library for commercial purposes.
SparkFun-Capacitors: Licensing: Creative Commons ShareAlike 4.0 International - https://creativecommons.org/licenses/by-sa/4.0
